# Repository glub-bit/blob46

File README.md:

# blob46
This a reversable 100x100mm pcb split keyboard with a number row. Compatible with choc v2 switches and has a gasket mounted case.

# Bill of Materials

| Component | Quantity | Link | Price |
| --------- | -------- | ---- | ----- |
| SMD diodes 0805 | 46 | https://www.aliexpress.us/item/3256806974248533.html?spm= | $1.66 |
| RP2040 zero | 2 | https://www.aliexpress.us/item/3256808552177000.html?spm= | $4.78 |
| M2 5mm screws | 12 | https://www.aliexpress.us/item/2251832624557792.html?spm= | $1.41 |
| M2 heated inserts Length: 3mm OD: 4mm | 12 | https://www.aliexpress.us/item/3256803396040989.html?spm= | $1.69 |
| PJ-320A | 2 | https://www.aliexpress.us/item/3256805376463085.html?spm= | $1.21 |
| TRRS male to male cable | 2 | https://www.aliexpress.us/item/3256809654236904.html?spm= | $2.78 |
| Poron foam 3mm thickness | 24-28 | https://www.aliexpress.us/item/3256806077981729.html?spm=](https://www.aliexpress.us/item/3256803420779042.html?spm= | $2.24 |

*pricing may change

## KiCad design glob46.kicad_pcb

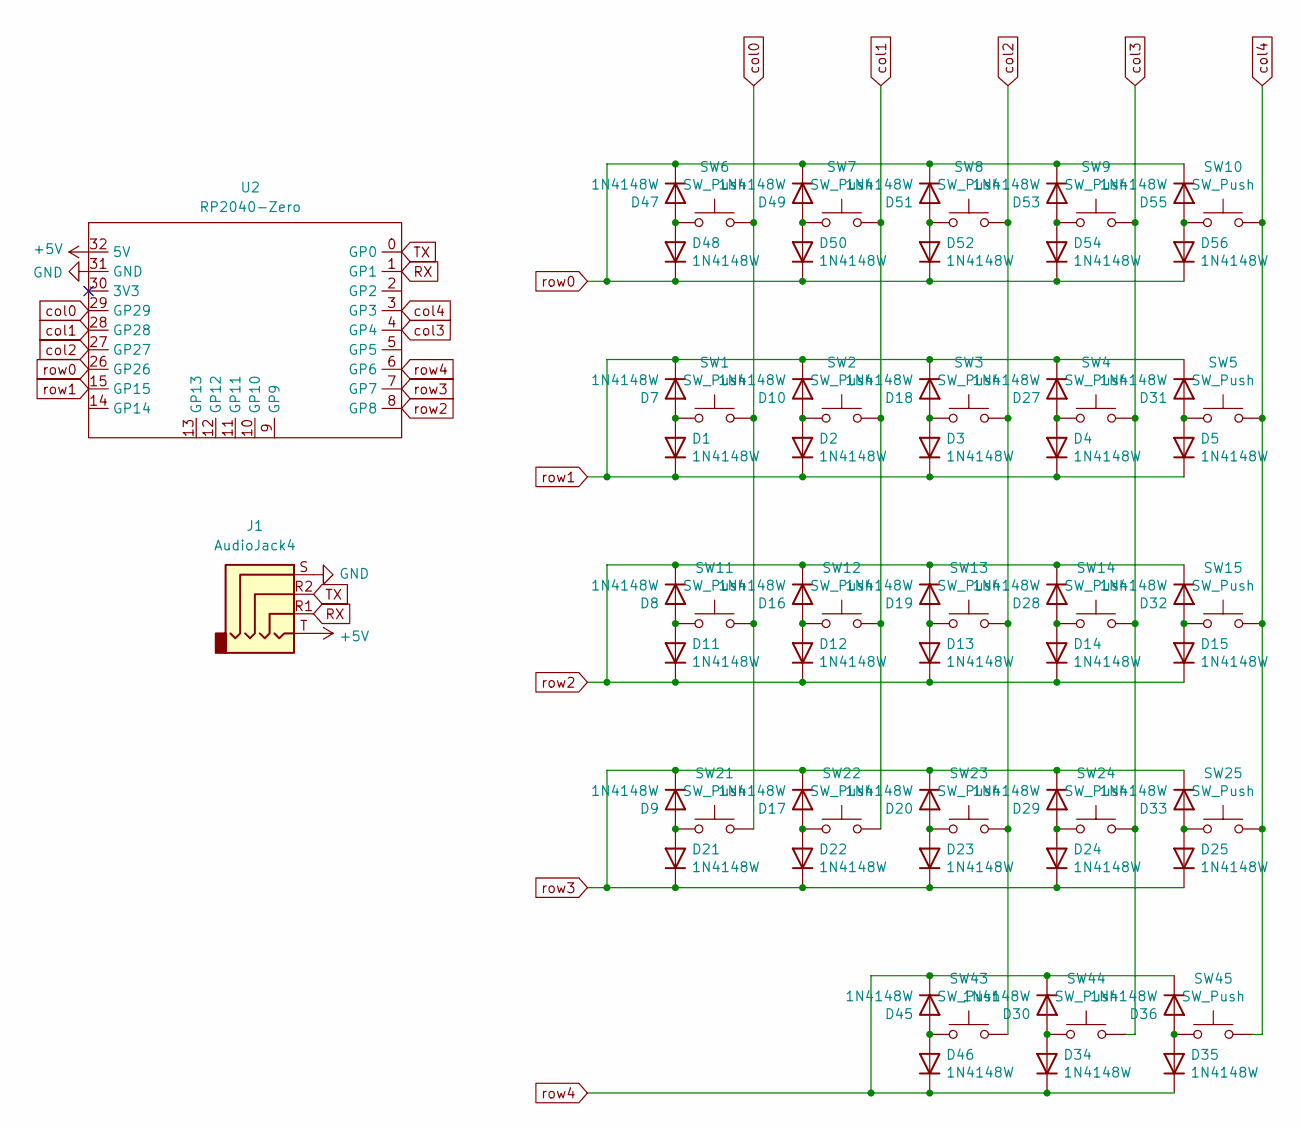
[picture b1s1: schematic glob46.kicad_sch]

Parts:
D1, D2, D3, D4, D5, D7, D8, D9, D10, D11, D12, D13, D14, D15, D16, D17, D18, D19, D20, D21, D22, D23, D24, D25, D27, D28, D29, D30, D31, D32, D33, D34, D35, D36, D45, D46, D47, D48, D49, D50, D51, D52, D53, D54, D55, D56: 1N4148W; D_SOD-123; LCSC C727110
J1: AudioJack4; CON_MJ-4PP-9_Reversible
SW1, SW2, SW3, SW4, SW5, SW6, SW7, SW8, SW9, SW10, SW11, SW12, SW13, SW14, SW15, SW21, SW22, SW23, SW24, SW25, SW43, SW44, SW45: SW_Push; SW_Kailh_Choc_V2_1.00u
U2: RP2040-Zero; MCU_RP2040_Zero_34

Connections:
+5V: J1.T, U2.32 (5V)
GND: J1.S, U2.31 (GND)
unnamed: D1.2 (A), D7.2 (A), SW1.1
unnamed: D2.2 (A), D10.2 (A), SW2.1
unnamed: D8.2 (A), D11.2 (A), SW11.1
unnamed: D12.2 (A), D16.2 (A), SW12.1
unnamed: D13.2 (A), D19.2 (A), SW13.1
unnamed: D14.2 (A), D28.2 (A), SW14.1
unnamed: D15.2 (A), D32.2 (A), SW15.1
unnamed: D17.2 (A), D22.2 (A), SW22.1
unnamed: D3.2 (A), D18.2 (A), SW3.1
unnamed: D20.2 (A), D23.2 (A), SW23.1
unnamed: D9.2 (A), D21.2 (A), SW21.1
unnamed: D24.2 (A), D29.2 (A), SW24.1
unnamed: D25.2 (A), D33.2 (A), SW25.1
unnamed: D4.2 (A), D27.2 (A), SW4.1
unnamed: D30.2 (A), D34.2 (A), SW44.1
unnamed: D5.2 (A), D31.2 (A), SW5.1
unnamed: D35.2 (A), D36.2 (A), SW45.1
unnamed: D45.2 (A), D46.2 (A), SW43.1
unnamed: D47.2 (A), D48.2 (A), SW6.1
unnamed: D49.2 (A), D50.2 (A), SW7.1
unnamed: D51.2 (A), D52.2 (A), SW8.1
unnamed: D53.2 (A), D54.2 (A), SW9.1
unnamed: D55.2 (A), D56.2 (A), SW10.1
RX: J1.R1, U2.1 (GP1)
TX: J1.R2, U2.0 (GP0)
col0: SW1.2, SW6.2, SW11.2, SW21.2, U2.29 (GP29)
col1: SW2.2, SW7.2, SW12.2, SW22.2, U2.28 (GP28)
col2: SW3.2, SW8.2, SW13.2, SW23.2, SW43.2, U2.27 (GP27)
col3: SW4.2, SW9.2, SW14.2, SW24.2, SW44.2, U2.4 (GP4)
col4: SW5.2, SW10.2, SW15.2, SW25.2, SW45.2, U2.3 (GP3)
row0: D47.1 (K), D48.1 (K), D49.1 (K), D50.1 (K), D51.1 (K), D52.1 (K), D53.1 (K), D54.1 (K), D55.1 (K), D56.1 (K), U2.26 (GP26)
row1: D1.1 (K), D2.1 (K), D3.1 (K), D4.1 (K), D5.1 (K), D7.1 (K), D10.1 (K), D18.1 (K), D27.1 (K), D31.1 (K), U2.15 (GP15)
row2: D8.1 (K), D11.1 (K), D12.1 (K), D13.1 (K), D14.1 (K), D15.1 (K), D16.1 (K), D19.1 (K), D28.1 (K), D32.1 (K), U2.8 (GP8)
row3: D9.1 (K), D17.1 (K), D20.1 (K), D21.1 (K), D22.1 (K), D23.1 (K), D24.1 (K), D25.1 (K), D29.1 (K), D33.1 (K), U2.7 (GP7)
row4: D30.1 (K), D34.1 (K), D35.1 (K), D36.1 (K), D45.1 (K), D46.1 (K), U2.6 (GP6)

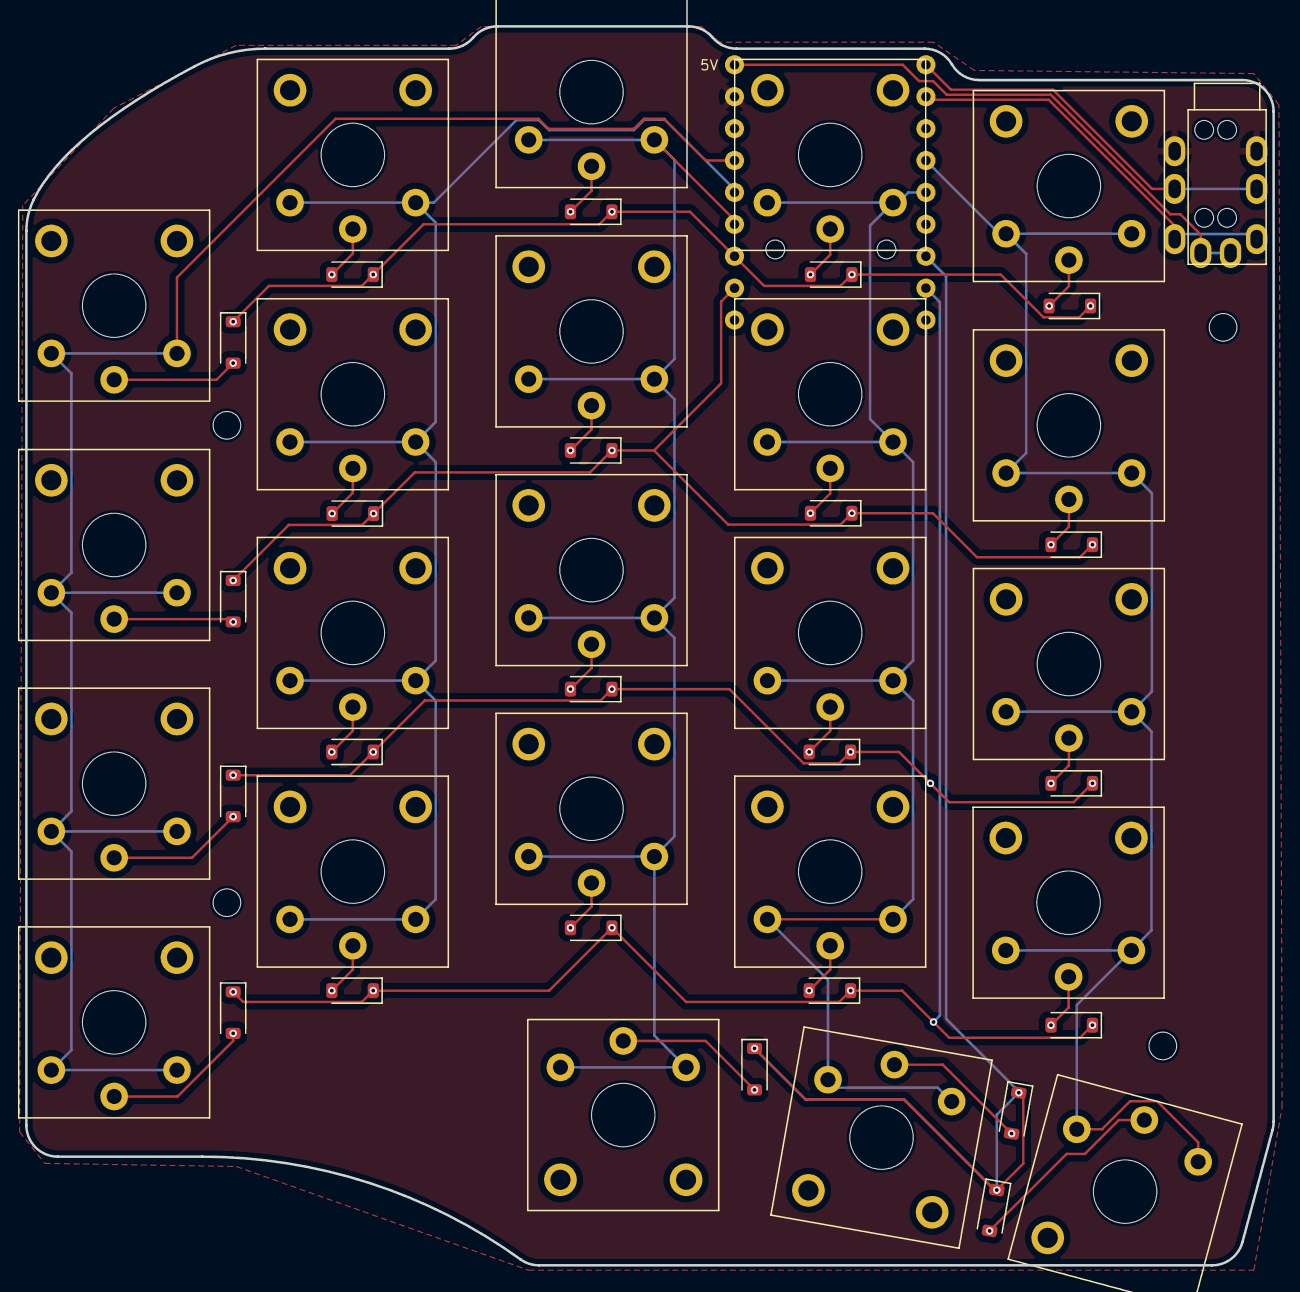
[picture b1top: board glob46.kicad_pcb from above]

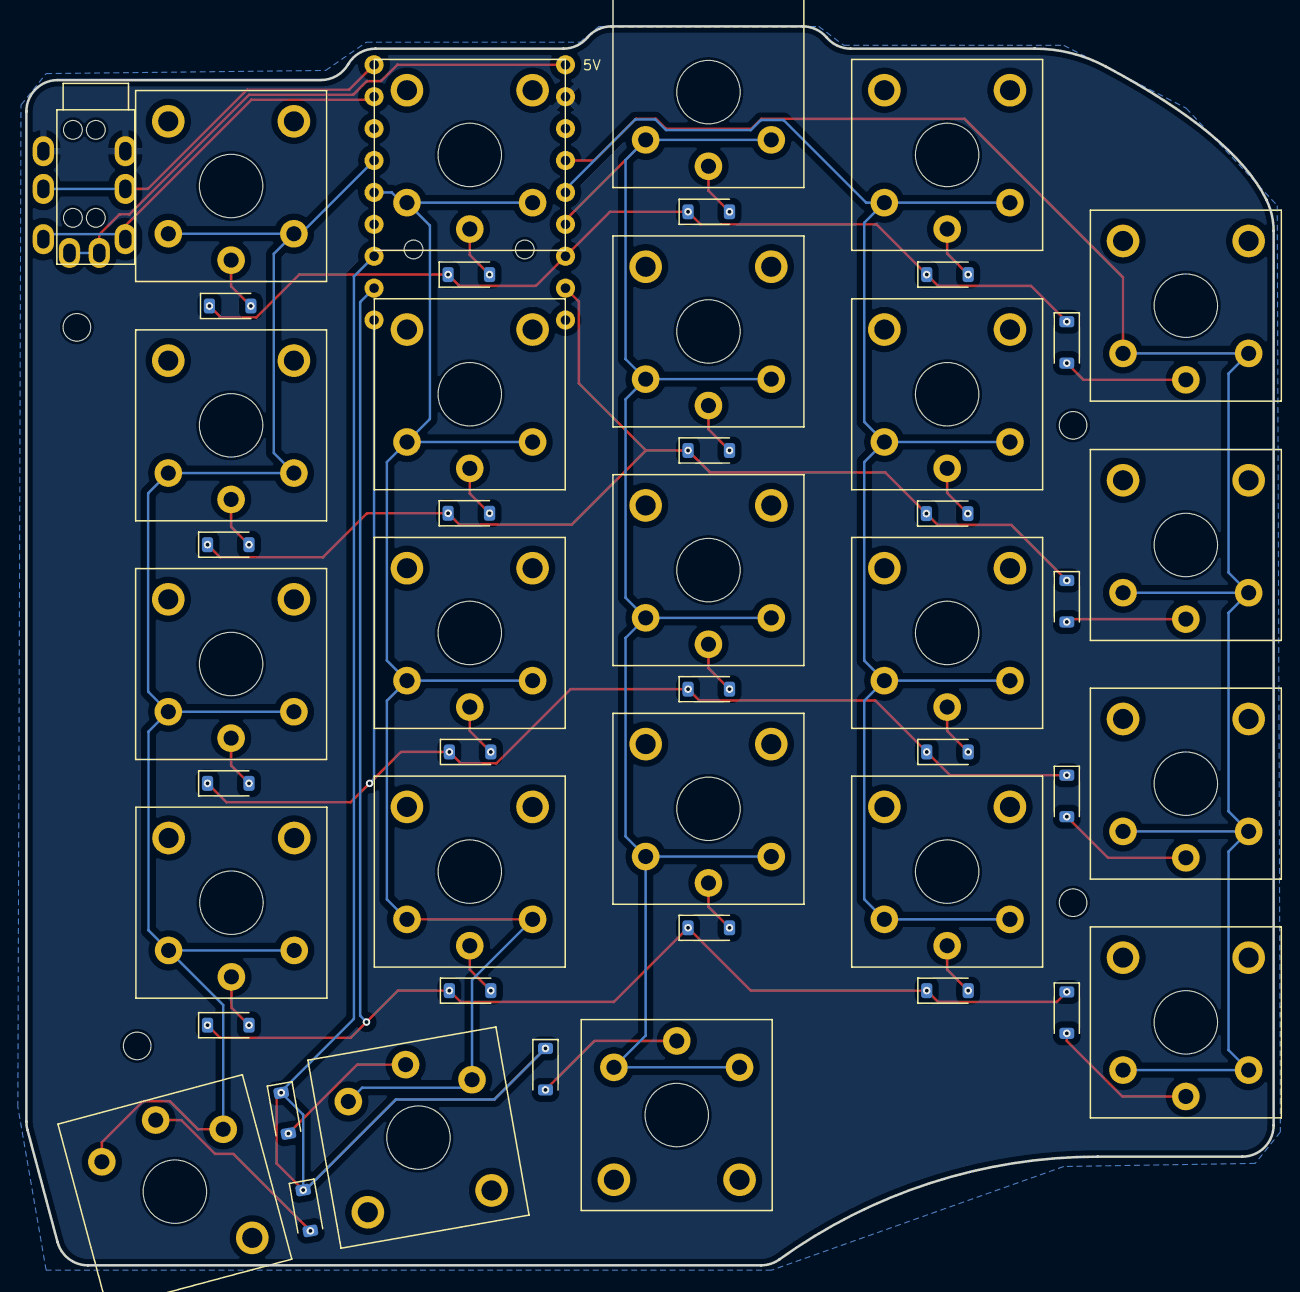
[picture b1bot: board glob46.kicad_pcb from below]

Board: 2 copper layers, 99.3 x 98.6 mm, 71 parts (23 on the bottom side), 37 nets.
